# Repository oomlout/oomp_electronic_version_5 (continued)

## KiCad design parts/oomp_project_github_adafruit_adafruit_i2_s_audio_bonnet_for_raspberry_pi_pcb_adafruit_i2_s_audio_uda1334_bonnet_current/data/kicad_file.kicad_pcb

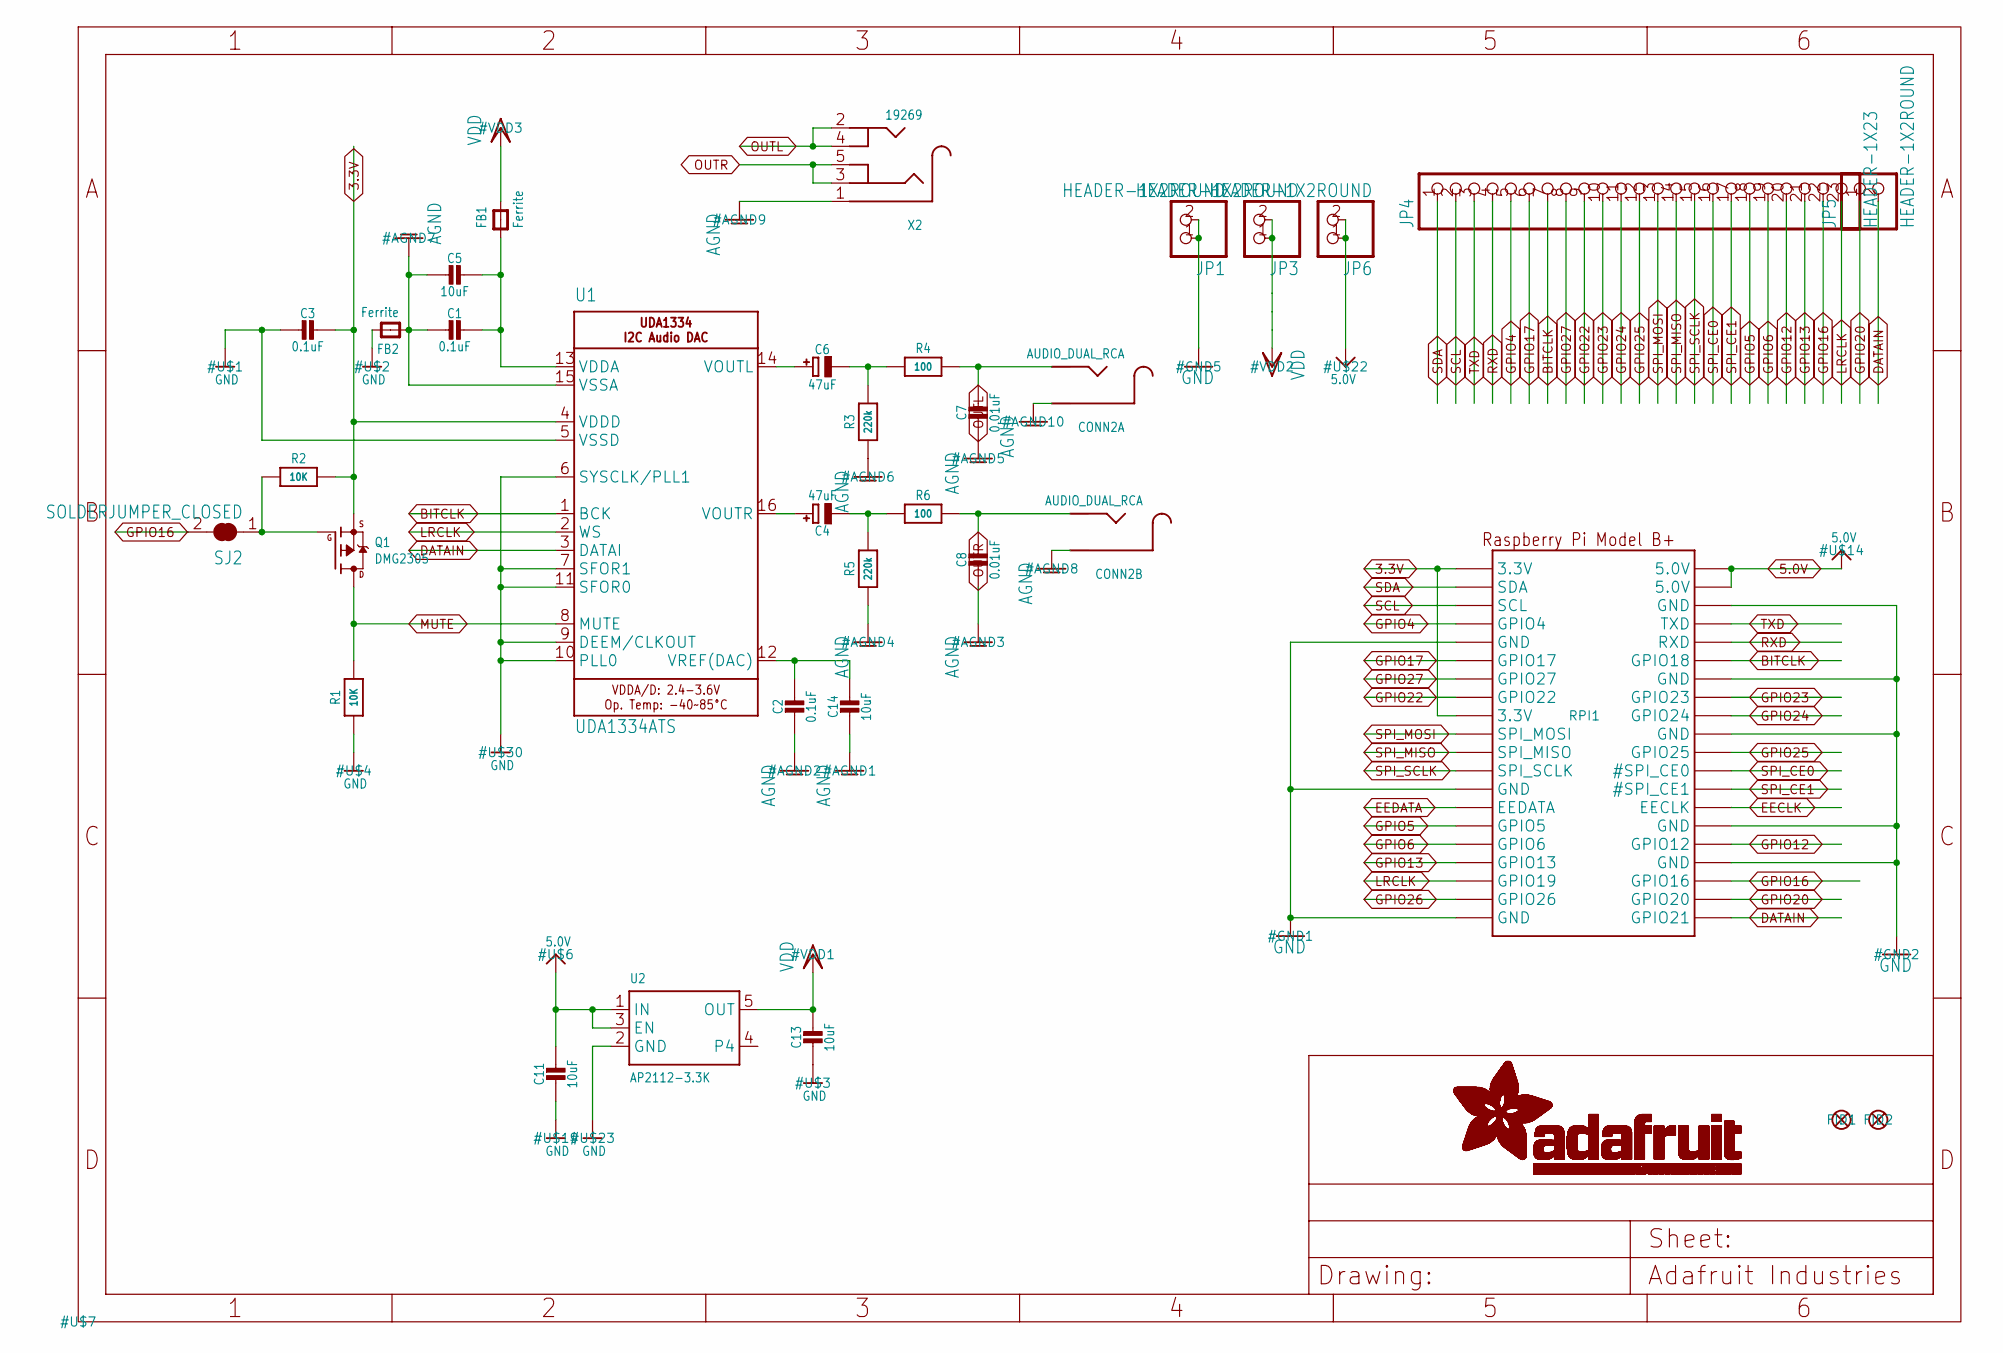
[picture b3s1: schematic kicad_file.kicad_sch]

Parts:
C1, C2, C3: 0.1uF; 0603-NO
C4, C6: 47uF; PANASONIC_C
C5, C11, C13, C14: 10uF; 0805-NO
C7, C8: 0.01uF; 0603-NO
CONN2: AUDIO_DUAL_RCA; RCA_DUAL_JACK
FB1, FB2: Ferrite; 0805
FID1, FID2: FIDUCIAL_1MM
JP1, JP3, JP5, JP6: HEADER-1X2ROUND; 1X02_ROUND
JP4: HEADER-1X23; 1X23_ROUND_70MIL
Q1: DMG2305; SOT23-WIDE
R1, R2: 10K; 0603-NO
R3, R5: 220k; 0603-NO
R4, R6: 100; 0603-NO
RPI1: RASPBERRYPI_BPLUS_BONNET_THMSMT; PI_BONNET_THMSMT
SJ2: SOLDERJUMPER_CLOSED; SOLDERJUMPER_CLOSEDWIRE
U1: UDA1334ATS; SSOP16_4.4MM
U2: AP2112-3.3K; SOT23-5
X2: 19269; 4UCONN_19269

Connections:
3.3V: C3.1, Q1.2 (S), R2.2, RPI1.1 (3.3V), RPI1.17 (3.3V), RPI1.S1 (3.3V), RPI1.S17 (3.3V), U1.4 (VDDD)
5.0V: C11.1, JP6.1, JP6.2, RPI1.2 (5.0V), RPI1.4 (5.0V), RPI1.S2 (5.0V), RPI1.S4 (5.0V), U2.1 (IN), U2.3 (EN)
AGND: C1.2, C2.2, C5.2, C7.2, C8.2, C14.2, CONN2.L_G (SLEEVE), CONN2.L_G' (SLEEVE), CONN2.R_G (SLEEVE), CONN2.R_G' (SLEEVE), FB2.1, R3.1, R5.1, U1.15 (VSSA), X2.1
BITCLK: JP4.7, RPI1.12 (GPIO18), RPI1.S12 (GPIO18), U1.1 (BCK)
DATAIN: JP5.2, RPI1.40 (GPIO21), RPI1.S40 (GPIO21), U1.3 (DATAI)
EECLK: RPI1.28 (EECLK), RPI1.S28 (EECLK)
EEDATA: RPI1.27 (EEDATA), RPI1.S27 (EEDATA)
GND: C3.2, C11.2, C13.2, FB2.2, JP1.1, JP1.2, R1.1, RPI1.6 (GND), RPI1.9 (GND), RPI1.14 (GND), RPI1.20 (GND), RPI1.25 (GND), RPI1.30 (GND), RPI1.34 (GND), RPI1.39 (GND), RPI1.S6 (GND), RPI1.S9 (GND), RPI1.S14 (GND), RPI1.S20 (GND), RPI1.S25 (GND), RPI1.S30 (GND), RPI1.S34 (GND), RPI1.S39 (GND), U1.5 (VSSD), U1.6 (SYSCLK/PLL1), U1.7 (SFOR1), U1.9 (DEEM/CLKOUT), U1.10 (PLL0), U1.11 (SFOR0), U2.2 (GND)
GPIO4: JP4.5, RPI1.7 (GPIO4), RPI1.S7 (GPIO4)
GPIO5: JP4.18, RPI1.29 (GPIO5), RPI1.S29 (GPIO5)
GPIO6: JP4.19, RPI1.31 (GPIO6), RPI1.S31 (GPIO6)
GPIO12: JP4.20, RPI1.32 (GPIO12), RPI1.S32 (GPIO12)
GPIO13: JP4.21, RPI1.33 (GPIO13), RPI1.S33 (GPIO13)
GPIO16: JP4.22, RPI1.36 (GPIO16), RPI1.S36 (GPIO16), SJ2.2
GPIO17: JP4.6, RPI1.11 (GPIO17), RPI1.S11 (GPIO17)
GPIO20: JP5.1, RPI1.38 (GPIO20), RPI1.S38 (GPIO20)
GPIO22: JP4.9, RPI1.15 (GPIO22), RPI1.S15 (GPIO22)
GPIO23: JP4.10, RPI1.16 (GPIO23), RPI1.S16 (GPIO23)
GPIO24: JP4.11, RPI1.18 (GPIO24), RPI1.S18 (GPIO24)
GPIO25: JP4.12, RPI1.22 (GPIO25), RPI1.S22 (GPIO25)
GPIO26: RPI1.37 (GPIO26), RPI1.S37 (GPIO26)
GPIO27: JP4.8, RPI1.13 (GPIO27), RPI1.S13 (GPIO27)
LRCLK: JP4.23, RPI1.35 (GPIO19), RPI1.S35 (GPIO19), U1.2 (WS)
MUTE: Q1.3 (D), R1.2, U1.8 (MUTE)
unnamed: C2.1, C14.1, U1.12 (VREF(DAC))
unnamed: C1.1, C5.1, FB1.1, U1.13 (VDDA)
unnamed: C4.+, U1.16 (VOUTR)
unnamed: Q1.1 (G), R2.1, SJ2.1
unnamed: C6.+, U1.14 (VOUTL)
unnamed: C6.-, R3.2, R4.1
unnamed: C4.-, R5.2, R6.1
OUTL: C7.1, CONN2.L_SIG (TIP), CONN2.L_SIG' (TIP), R4.2, X2.2, X2.4
OUTR: C8.1, CONN2.R_SIG (TIP), CONN2.R_SIG' (TIP), R6.2, X2.3, X2.5
RXD: JP4.4, RPI1.10 (RXD), RPI1.S10 (RXD)
SCL: JP4.2, RPI1.5 (SCL), RPI1.S5 (SCL)
SDA: JP4.1, RPI1.3 (SDA), RPI1.S3 (SDA)
SPI_CE0: JP4.16, RPI1.24 (#SPI_CE0), RPI1.S24 (#SPI_CE0)
SPI_CE1: JP4.17, RPI1.26 (#SPI_CE1), RPI1.S26 (#SPI_CE1)
SPI_MISO: JP4.14, RPI1.21 (SPI_MISO), RPI1.S21 (SPI_MISO)
SPI_MOSI: JP4.13, RPI1.19 (SPI_MOSI), RPI1.S19 (SPI_MOSI)
SPI_SCLK: JP4.15, RPI1.23 (SPI_SCLK), RPI1.S23 (SPI_SCLK)
TXD: JP4.3, RPI1.8 (TXD), RPI1.S8 (TXD)
VDD: C13.1, FB1.2, JP3.1, JP3.2, U2.5 (OUT)

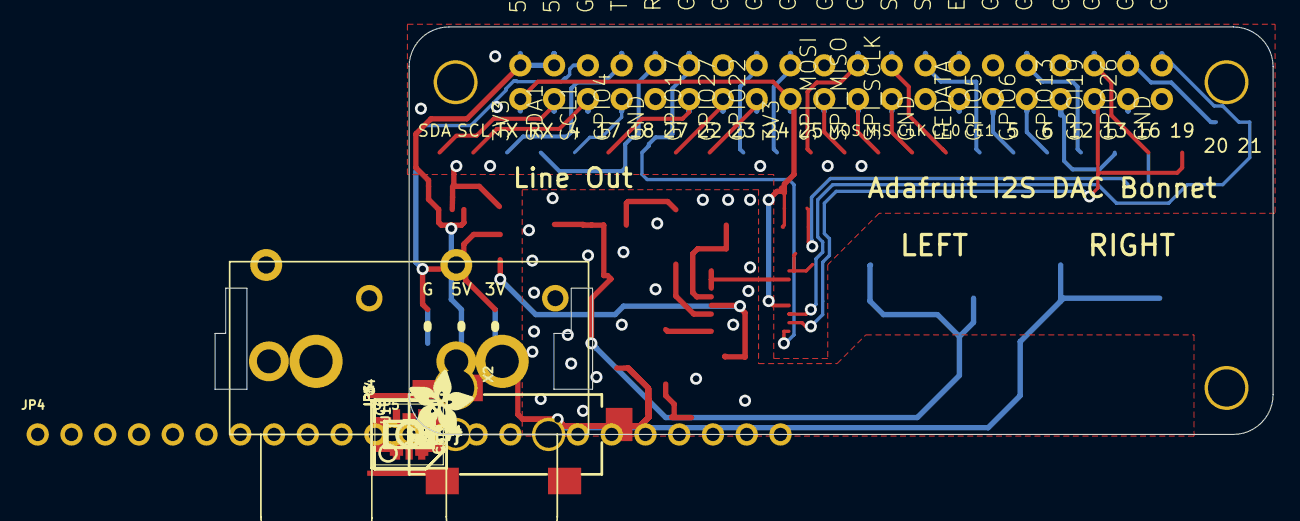
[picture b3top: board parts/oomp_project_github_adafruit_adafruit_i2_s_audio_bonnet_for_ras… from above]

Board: 2 copper layers, 65.0 x 30.7 mm, 35 parts (1 on the bottom side), 43 nets.

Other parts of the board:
U$5: ADAFRUIT_5MM
U$11: PCBFEAT-REV-040

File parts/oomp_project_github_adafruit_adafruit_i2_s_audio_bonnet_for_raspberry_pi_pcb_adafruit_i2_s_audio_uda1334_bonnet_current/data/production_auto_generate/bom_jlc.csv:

Comment,Designator,Footprint,LCSC Part #
,"JP1,JP3,JP5,JP6",Adafruit I2S Audio UDA1334 Bonnet-import-fps:1X02_ROUND,C492401
,JP4,Adafruit I2S Audio UDA1334 Bonnet-import-fps:1X23_ROUND_70MIL,C725915
,U$5,Adafruit I2S Audio UDA1334 Bonnet-import-fps:ADAFRUIT_5MM,
,U$11,Adafruit I2S Audio UDA1334 Bonnet-import-fps:PCBFEAT-REV-040,
 DMG2305,Q1,Adafruit I2S Audio UDA1334 Bonnet-import-fps:SOT23-WIDE,
0.01uF,"C7,C8",Adafruit I2S Audio UDA1334 Bonnet-import-fps:0603-NO,C5137477
0.1uF,"C1,C2,C3",Adafruit I2S Audio UDA1334 Bonnet-import-fps:0603-NO,C14663
100,"R4,R6",Adafruit I2S Audio UDA1334 Bonnet-import-fps:0603-NO,C22775
10K,"R1,R2",Adafruit I2S Audio UDA1334 Bonnet-import-fps:0603-NO,C98220
10uF,"C5,C11,C13,C14",Adafruit I2S Audio UDA1334 Bonnet-import-fps:0805-NO,
19269,X2,Adafruit I2S Audio UDA1334 Bonnet-import-fps:4UCONN_19269,
220k,"R3,R5",Adafruit I2S Audio UDA1334 Bonnet-import-fps:0603-NO,C2907013
47uF,"C4,C6",Adafruit I2S Audio UDA1334 Bonnet-import-fps:PANASONIC_C,
AP2112-3.3K,U2,Adafruit I2S Audio UDA1334 Bonnet-import-fps:SOT23-5,
AUDIO_DUAL_RCA,CONN2,Adafruit I2S Audio UDA1334 Bonnet-import-fps:RCA_DUAL_JACK,
Ferrite,"FB1,FB2",Adafruit I2S Audio UDA1334 Bonnet-import-fps:0805,
RASPBERRYPI_BPLUS_BONNET_THMSMT,RPI1,Adafruit I2S Audio UDA1334 Bonnet-import-fps:PI_BONNET_THMSMT,
UDA1334ATS,U1,Adafruit I2S Audio UDA1334 Bonnet-import-fps:SSOP16_4.4MM,

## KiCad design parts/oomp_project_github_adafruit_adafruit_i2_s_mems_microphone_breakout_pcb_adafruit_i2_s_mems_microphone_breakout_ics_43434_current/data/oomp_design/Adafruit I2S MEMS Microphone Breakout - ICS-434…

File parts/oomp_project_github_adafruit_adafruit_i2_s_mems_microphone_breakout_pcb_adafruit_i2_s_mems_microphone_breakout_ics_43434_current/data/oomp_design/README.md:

# OOMP KiCad design copy

Open `Adafruit I2S MEMS Microphone Breakout - ICS-43434.kicad_pro` (or the `.kicad_pcb` / `.kicad_sch`) in KiCad. Local OOMP libraries are under `libraries/`. Original inputs are preserved in [../original/](../original/).

Only verified unchanged installed KiCad defaults were renamed. Modified, custom, unmatched and unavailable items remain unchanged. Soldering variants are never swapped during conversion. Existing pad coordinates, nets and UUIDs are preserved.

See [conversion_report.yaml](conversion_report.yaml) for every conversion and skip. Copy this directory before editing; regeneration refuses to overwrite edited design files.

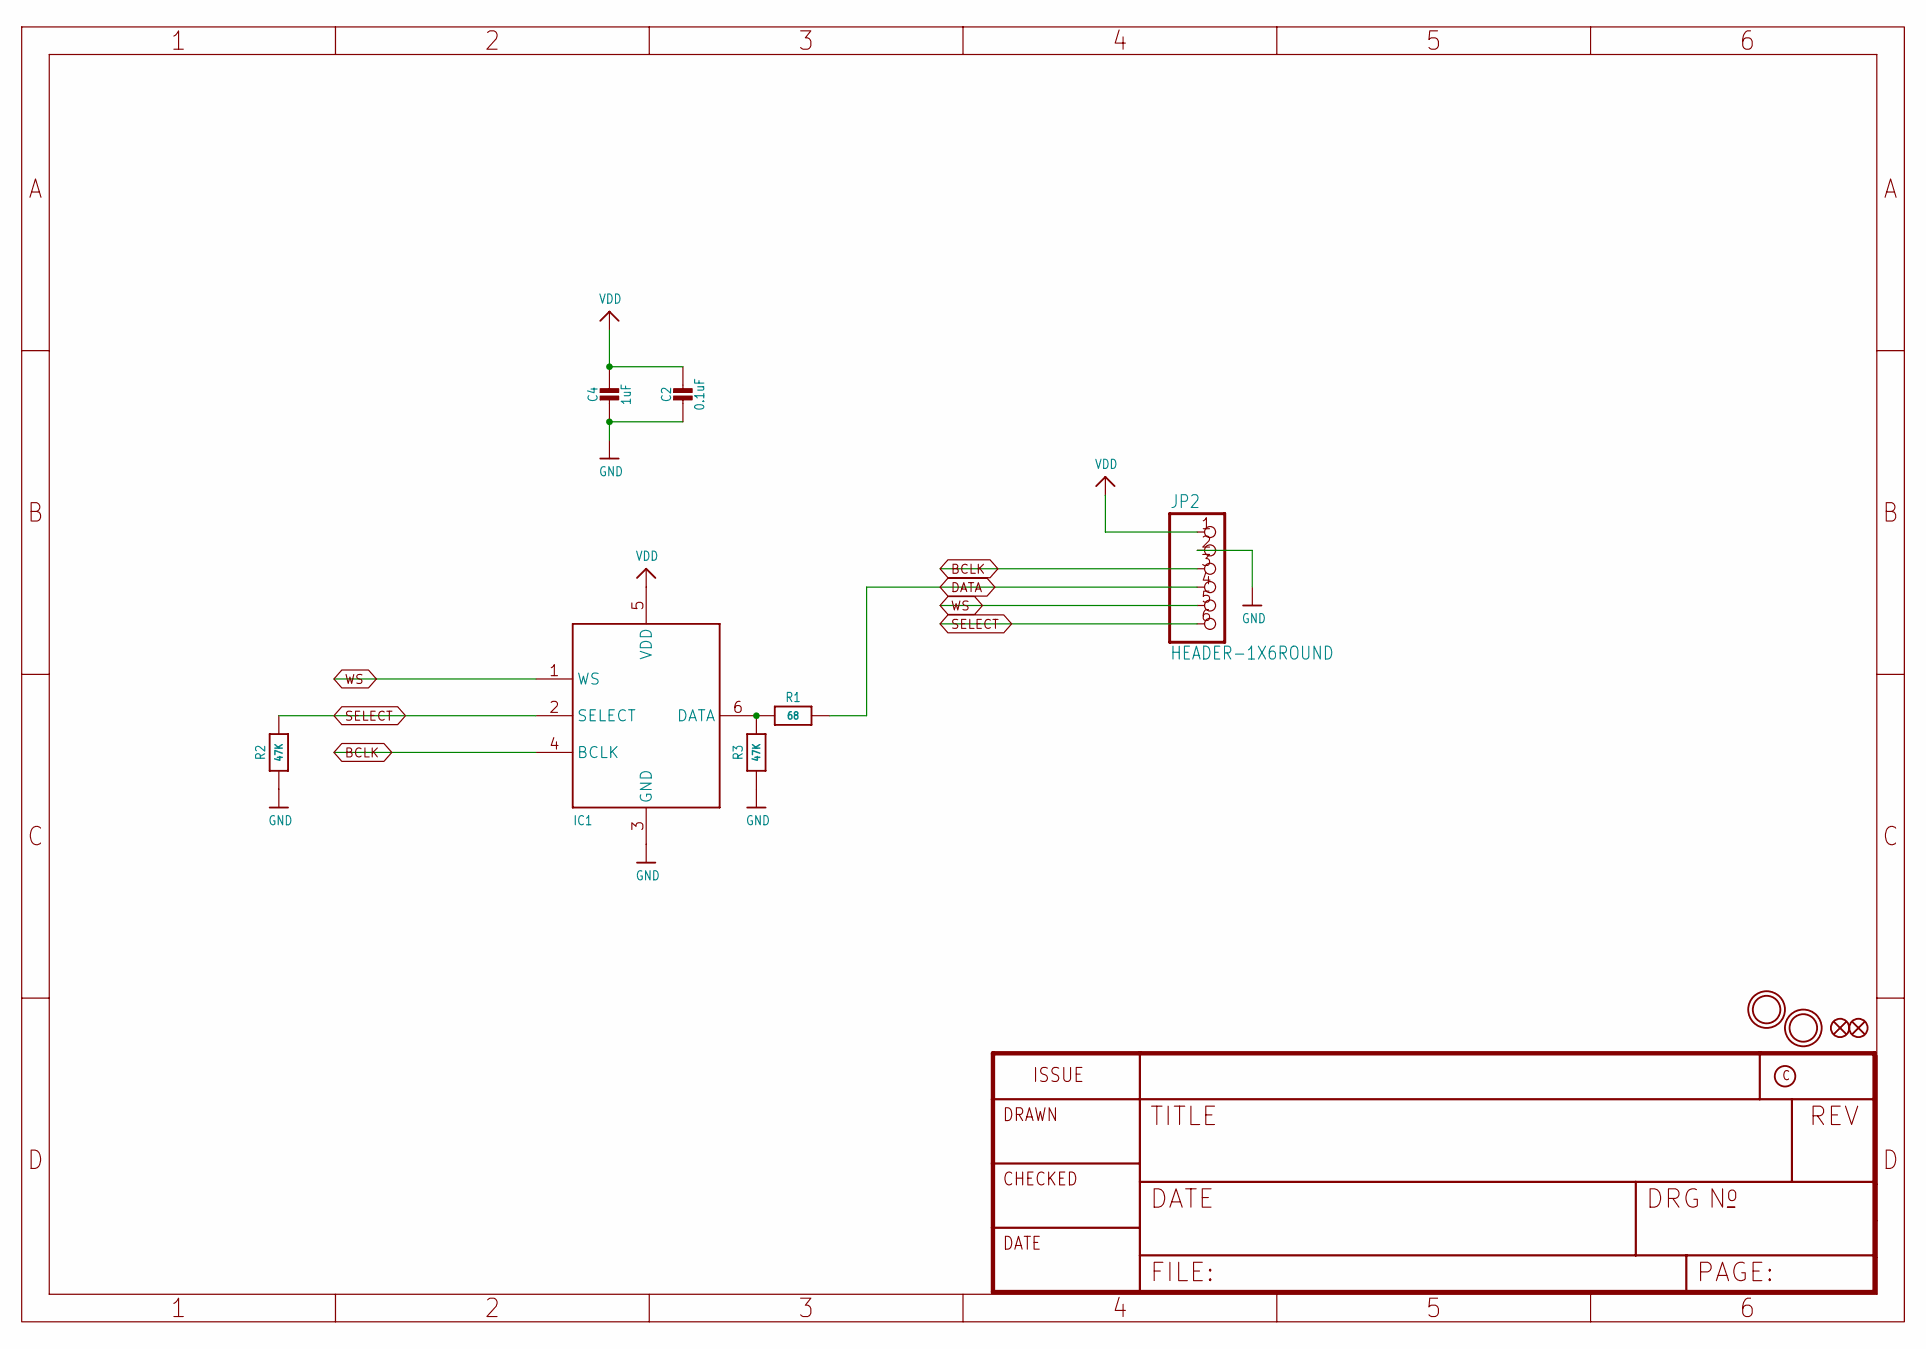
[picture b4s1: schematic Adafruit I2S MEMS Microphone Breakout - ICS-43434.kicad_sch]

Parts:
C2: 0.1uF; 0603-NO
C4: 1uF; 0603-NO
FID1, FID2: FIDUCIAL_0.5MM
IC1: ICS-43434; SPH0645LM4H
JP2: HEADER-1X6ROUND; 1X06_ROUND
R1: 68; 0603-NO
R2, R3: 47K; 0603-NO
U$6, U$12: MOUNTINGHOLE2.5; MOUNTINGHOLE_2.5_PLATED

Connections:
BCLK: IC1.4 (BCLK), JP2.3
DATA: JP2.4, R1.2
GND: C2.2, C4.2, IC1.3 (GND), JP2.2, R2.1, R3.1
unnamed: IC1.6 (DATA), R1.1, R3.2
SELECT: IC1.2 (SELECT), JP2.6, R2.2
VDD: C2.1, C4.1, IC1.5 (VDD), JP2.1
WS: IC1.1 (WS), JP2.5

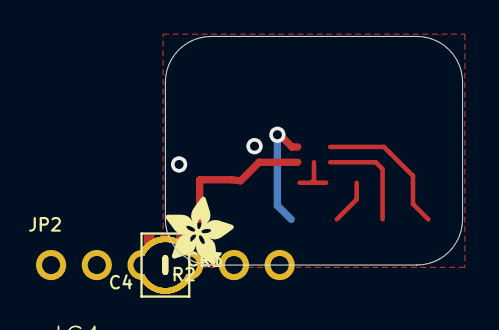
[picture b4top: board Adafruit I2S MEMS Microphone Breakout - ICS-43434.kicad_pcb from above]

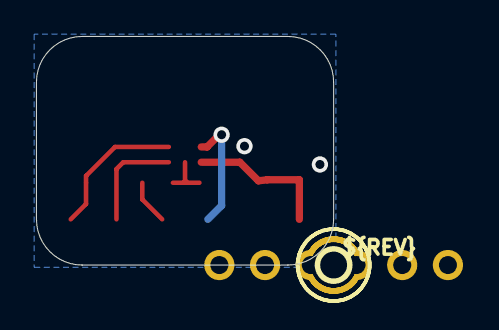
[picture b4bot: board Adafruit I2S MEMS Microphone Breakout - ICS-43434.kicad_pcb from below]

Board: 2 copper layers, 16.5 x 12.7 mm, 23 parts (11 on the bottom side), 7 nets.

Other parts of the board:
PLABEL0: PLABEL0
PLABEL1: PLABEL1
PLABEL2: PLABEL2
PLABEL3: PLABEL3
PLABEL4: PLABEL4
PLABEL5: PLABEL5
PLABEL7: PLABEL7
PLABEL8: PLABEL8
PLABEL9: PLABEL9
PLABEL10: PLABEL10
U$5: ADAFRUIT_3.5MM
U$13: PCBFEAT-REV-040

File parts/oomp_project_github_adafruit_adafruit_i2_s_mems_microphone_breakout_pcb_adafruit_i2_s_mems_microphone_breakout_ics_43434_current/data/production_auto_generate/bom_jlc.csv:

Comment,Designator,Footprint,LCSC Part #
,JP2,Adafruit I2S MEMS Microphone Breakout - ICS-43434-import-fps:1X06_ROUND,C37208
,U$5,Adafruit I2S MEMS Microphone Breakout - ICS-43434-import-fps:ADAFRUIT_3.5MM,
,U$13,Adafruit I2S MEMS Microphone Breakout - ICS-43434-import-fps:PCBFEAT-REV-040,
,PLABEL0,Adafruit I2S MEMS Microphone Breakout - ICS-43434-import-fps:PLABEL0,
,PLABEL1,Adafruit I2S MEMS Microphone Breakout - ICS-43434-import-fps:PLABEL1,
,PLABEL10,Adafruit I2S MEMS Microphone Breakout - ICS-43434-import-fps:PLABEL10,
,PLABEL2,Adafruit I2S MEMS Microphone Breakout - ICS-43434-import-fps:PLABEL2,
,PLABEL3,Adafruit I2S MEMS Microphone Breakout - ICS-43434-import-fps:PLABEL3,
,PLABEL4,Adafruit I2S MEMS Microphone Breakout - ICS-43434-import-fps:PLABEL4,
,PLABEL5,Adafruit I2S MEMS Microphone Breakout - ICS-43434-import-fps:PLABEL5,
,PLABEL7,Adafruit I2S MEMS Microphone Breakout - ICS-43434-import-fps:PLABEL7,
,PLABEL8,Adafruit I2S MEMS Microphone Breakout - ICS-43434-import-fps:PLABEL8,
,PLABEL9,Adafruit I2S MEMS Microphone Breakout - ICS-43434-import-fps:PLABEL9,
0.1uF,C2,Adafruit I2S MEMS Microphone Breakout - ICS-43434-import-fps:0603-NO,C14663
1uF,C4,Adafruit I2S MEMS Microphone Breakout - ICS-43434-import-fps:0603-NO,C5673
47K,"R2,R3",Adafruit I2S MEMS Microphone Breakout - ICS-43434-import-fps:0603-NO,C2907042
68,R1,Adafruit I2S MEMS Microphone Breakout - ICS-43434-import-fps:0603-NO,C27592
ICS-43434,IC1,Adafruit I2S MEMS Microphone Breakout - ICS-43434-import-fps:SPH0645LM4H,

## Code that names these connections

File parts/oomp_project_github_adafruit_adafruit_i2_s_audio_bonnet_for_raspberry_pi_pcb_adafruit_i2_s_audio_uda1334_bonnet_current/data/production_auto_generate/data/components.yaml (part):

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    y_mm: -21.209
  - name: '5'
    type: thru_hole
    net: GPIO4
    x_mm: 12.446
    y_mm: -21.209
  - name: '6'
    type: thru_hole
    net: GPIO17
    x_mm: 14.986
    y_mm: -21.209
  - name: '7'
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    y_mm: -21.209
  - name: '8'
    type: thru_hole
    net: GPIO27
    x_mm: 20.066
    y_mm: -21.209
  - name: '9'
    type: thru_hole
    net: GPIO22
    x_mm: 22.606
    y_mm: -21.209
  - name: '10'
    type: thru_hole
    net: GPIO23
    x_mm: 25.146
    y_mm: -21.209
  - name: '11'
    type: thru_hole
    net: GPIO24
    x_mm: 27.686
    y_mm: -21.209
  - name: '12'
    type: thru_hole
    net: GPIO25
    x_mm: 30.226
    y_mm: -21.209
  - name: '13'
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    y_mm: -21.209
  - name: '18'
    type: thru_hole
    net: GPIO5
    x_mm: 45.466
    y_mm: -21.209
  - name: '19'
    type: thru_hole
    net: GPIO6
    x_mm: 48.006
    y_mm: -21.209
  - name: '20'
    type: thru_hole
    net: GPIO12
    x_mm: 50.546
    y_mm: -21.209
  - name: '21'
    type: thru_hole
    net: GPIO13
    x_mm: 53.086
    y_mm: -21.209
  - name: '22'
    type: thru_hole
    net: GPIO16
    x_mm: 55.626
    y_mm: -21.209
  - name: '23'
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  pads:
  - name: '1'
    type: thru_hole
    net: GPIO20
    x_mm: 60.706
    y_mm: -23.495
  - name: '2'
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    y_mm: -27.77
  - name: '7'
    type: thru_hole
    net: GPIO4
    x_mm: 15.99
    y_mm: -25.23
  - name: '8'
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    y_mm: -27.77
  - name: '11'
    type: thru_hole
    net: GPIO17
    x_mm: 21.07
    y_mm: -25.23
  - name: '12'
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    y_mm: -27.77
  - name: '13'
    type: thru_hole
    net: GPIO27
    x_mm: 23.61
    y_mm: -25.23
  - name: '14'
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    y_mm: -27.77
  - name: '15'
    type: thru_hole
    net: GPIO22
    x_mm: 26.15
    y_mm: -25.23
  - name: '16'
    type: thru_hole
    net: GPIO23
    x_mm: 26.15
    y_mm: -27.77
  - name: '17'
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    y_mm: -25.23
  - name: '18'
    type: thru_hole
    net: GPIO24
    x_mm: 28.69
    y_mm: -27.77
  - name: '19'
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    y_mm: -25.23
  - name: '22'
    type: thru_hole
    net: GPIO25
    x_mm: 33.77
    y_mm: -27.77
  - name: '23'
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    y_mm: -27.77
  - name: '29'
    type: thru_hole
    net: GPIO5
    x_mm: 43.93
    y_mm: -25.23
  - name: '30'
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    y_mm: -27.77
  - name: '31'
    type: thru_hole
    net: GPIO6
    x_mm: 46.47
    y_mm: -25.23
  - name: '32'
    type: thru_hole
    net: GPIO12
    x_mm: 46.47
    y_mm: -27.77
  - name: '33'
    type: thru_hole
    net: GPIO13
    x_mm: 49.01
    y_mm: -25.23
  - name: '34'
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    y_mm: -25.23
  - name: '36'
    type: thru_hole
    net: GPIO16
    x_mm: 51.55
    y_mm: -27.77
  - name: '37'
    type: thru_hole
    net: GPIO26
    x_mm: 54.09
    y_mm: -25.23
  - name: '38'
    type: thru_hole
    net: GPIO20
    x_mm: 54.09
    y_mm: -27.77
  - name: '39'
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    y_mm: -28.6574
  - name: S7
    type: smd
    net: GPIO4
    x_mm: 15.9896
    y_mm: -24.3394
  - name: S8
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    y_mm: -28.6574
  - name: S11
    type: smd
    net: GPIO17
    x_mm: 21.0696
    y_mm: -24.3394
  - name: S12
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    y_mm: -28.6574
  - name: S13
    type: smd
    net: GPIO27
    x_mm: 23.6096
    y_mm: -24.3394
  - name: S14
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    y_mm: -28.6574
  - name: S15
    type: smd
    net: GPIO22
    x_mm: 26.1496
    y_mm: -24.3394
  - name: S16
    type: smd
    net: GPIO23
    x_mm: 26.1496
    y_mm: -28.6574
  - name: S17
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    y_mm: -24.3394
  - name: S18
    type: smd
    net: GPIO24
    x_mm: 28.6896
    y_mm: -28.6574
  - name: S19
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    y_mm: -24.3394
  - name: S22
    type: smd
    net: GPIO25
    x_mm: 33.7696
    y_mm: -28.6574
  - name: S23
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    y_mm: -28.6574
  - name: S29
    type: smd
    net: GPIO5
    x_mm: 43.9296
    y_mm: -24.3394
  - name: S30
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    y_mm: -28.6574
  - name: S31
    type: smd
    net: GPIO6
    x_mm: 46.4696
    y_mm: -24.3394
  - name: S32
    type: smd
    net: GPIO12
    x_mm: 46.4696
    y_mm: -28.6574
  - name: S33
    type: smd
    net: GPIO13
    x_mm: 49.0096
    y_mm: -24.3394
  - name: S34
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    y_mm: -24.3394
  - name: S36
    type: smd
    net: GPIO16
    x_mm: 51.5496
    y_mm: -28.6574
  - name: S37
    type: smd
    net: GPIO26
    x_mm: 54.0896
    y_mm: -24.3394
  - name: S38
    type: smd
    net: GPIO20
    x_mm: 54.0896
    y_mm: -28.6574
  - name: S39
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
